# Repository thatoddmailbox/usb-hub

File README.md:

# usb-hub

A four-port USB 2.0 hub based around the [CoreChips SL2.1A](https://datasheet.lcsc.com/szlcsc/1811151645_CoreChips-SL2-1A_C192893.pdf) IC.

You can choose whether it's bus powered or externally powered with JP1. Soldering JP1 closed selects bus power, while leaving JP1 open means devices are powered with external power, which can be provided through J2.

Note that an external 12 MHz crystal is provided for the SL2.1A. The datasheet claims that the chip also has an internal 12 MHz oscillator that you can use by connecting XIN (pin 16 of the SL2.1) to ground. It's recommended to use the external one, though, as it's more stable. (see the red Chinese text on page 5 of the datasheet)

The port closest to the upstream mini-USB port is port number 1, and the remaining ports are numbered 2 through 4.

## Assembly
This board is fairly easy to assemble with a soldering iron, flux, and solder wick. The main thing to watch out for is that the two sets of electrolytic capacitors, near the output ports, have opposite polarities. The silkscreen has the positive side labeled, so you should make sure the negative side of the capacitor (with the black stripe) is opposite of the positive side (as labeled by a plus on the board).

## Useful links
* [Rev 0 schematic](./mfg/rev0/usb-hub.pdf)
* [Rev 0 BOM](./mfg/rev0/usb-hub.csv)

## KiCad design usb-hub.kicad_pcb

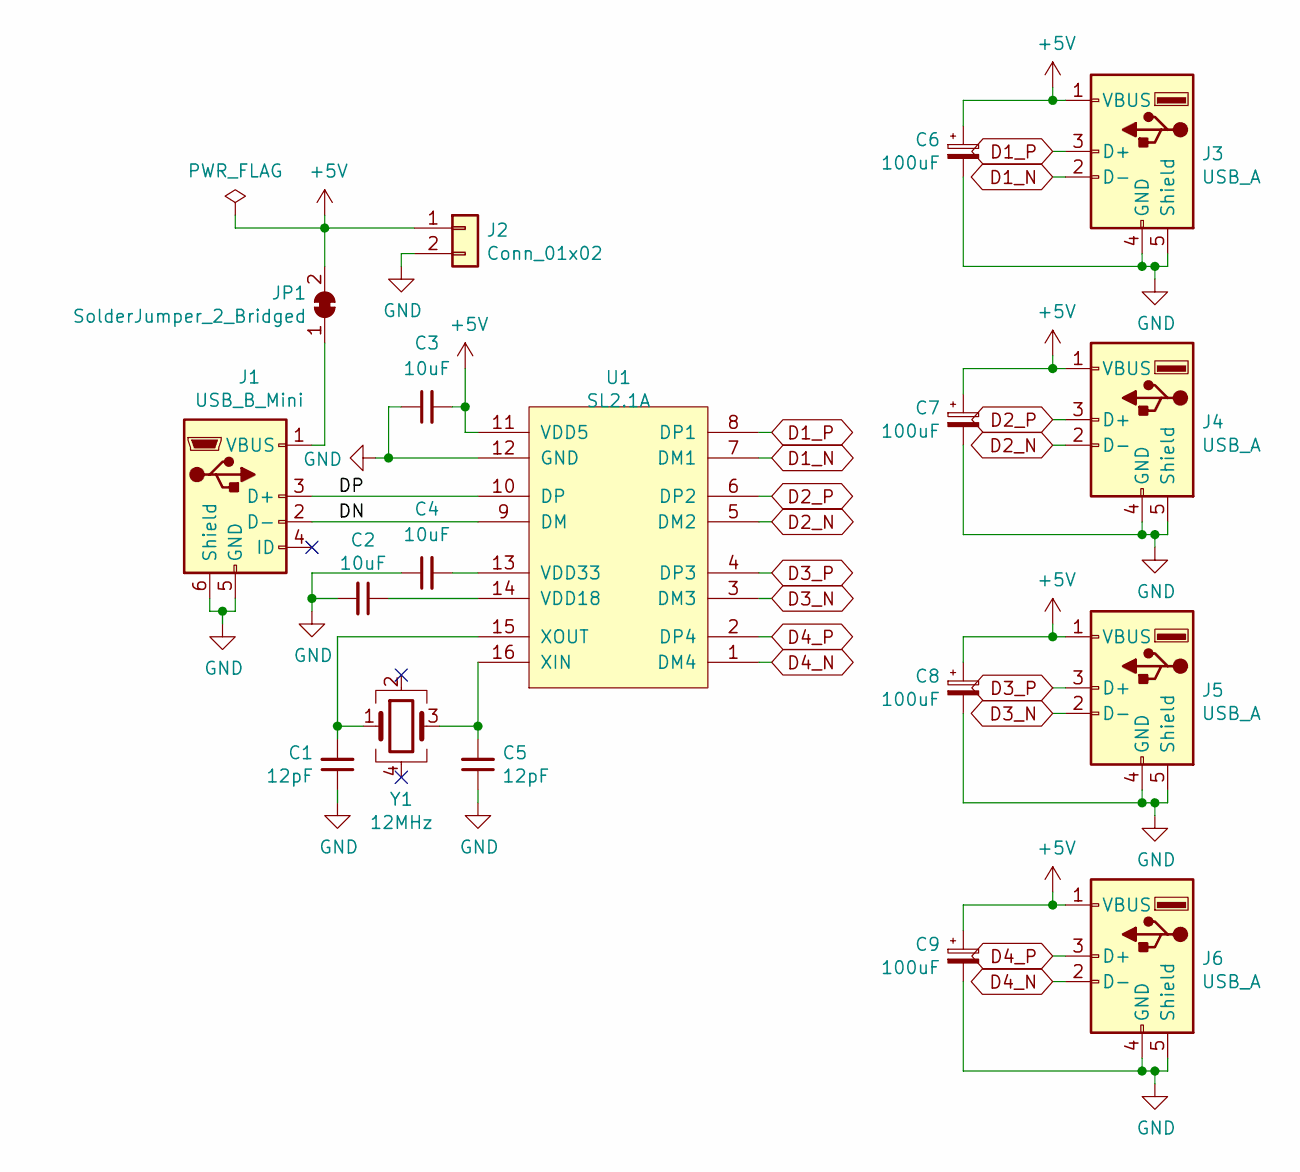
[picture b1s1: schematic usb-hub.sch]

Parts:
C1, C5: 12pF; C_0603_HandSoldering
C2, C3, C4: 10uF; C_0603_HandSoldering
C6, C7, C8, C9: 100uF; CP_Elec_6.3x5.3
J1: USB_B_Mini; USB_Mini-B
J2: Conn_01x02; Pin_Header_Straight_1x02_Pitch2.54mm
J3, J4, J5, J6: USB_A
JP1: SolderJumper_2_Bridged; SolderJumper-2_P1.3mm_Open_TrianglePad1.0x1.5mm
U1: SL2.1A; SOIC-16_3.9x9.9mm_Pitch1.27mm
Y1: 12MHz; Crystal_SMD_3225-4pin_3.2x2.5mm_HandSoldering

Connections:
+5V: C3.2, C6.1, C7.1, C8.1, C9.1, J2.1, J3.1 (VBUS), J4.1 (VBUS), J5.1 (VBUS), J6.1 (VBUS), JP1.2 (B), U1.11 (VDD5)
/DN: J1.2 (D-), U1.9 (DM)
/DP: J1.3 (D+), U1.10 (DP)
D1_N: J3.2 (D-), U1.7 (DM1)
D1_P: J3.3 (D+), U1.8 (DP1)
D2_N: J4.2 (D-), U1.5 (DM2)
D2_P: J4.3 (D+), U1.6 (DP2)
D3_N: J5.2 (D-), U1.3 (DM3)
D3_P: J5.3 (D+), U1.4 (DP3)
D4_N: J6.2 (D-), U1.1 (DM4)
D4_P: J6.3 (D+), U1.2 (DP4)
GND: C1.1, C2.2, C3.1, C4.1, C5.1, C6.2, C7.2, C8.2, C9.2, J1.5 (GND), J1.6 (Shield), J2.2, J3.4 (GND), J3.5 (Shield), J4.4 (GND), J4.5 (Shield), J5.4 (GND), J5.5 (Shield), J6.4 (GND), J6.5 (Shield), U1.12 (GND)
unnamed: C1.2, U1.15 (XOUT), Y1.1
unnamed: C2.1, U1.14 (VDD18)
unnamed: C4.2, U1.13 (VDD33)
unnamed: C5.2, U1.16 (XIN), Y1.3
unnamed: J1.1 (VBUS), JP1.1 (A)

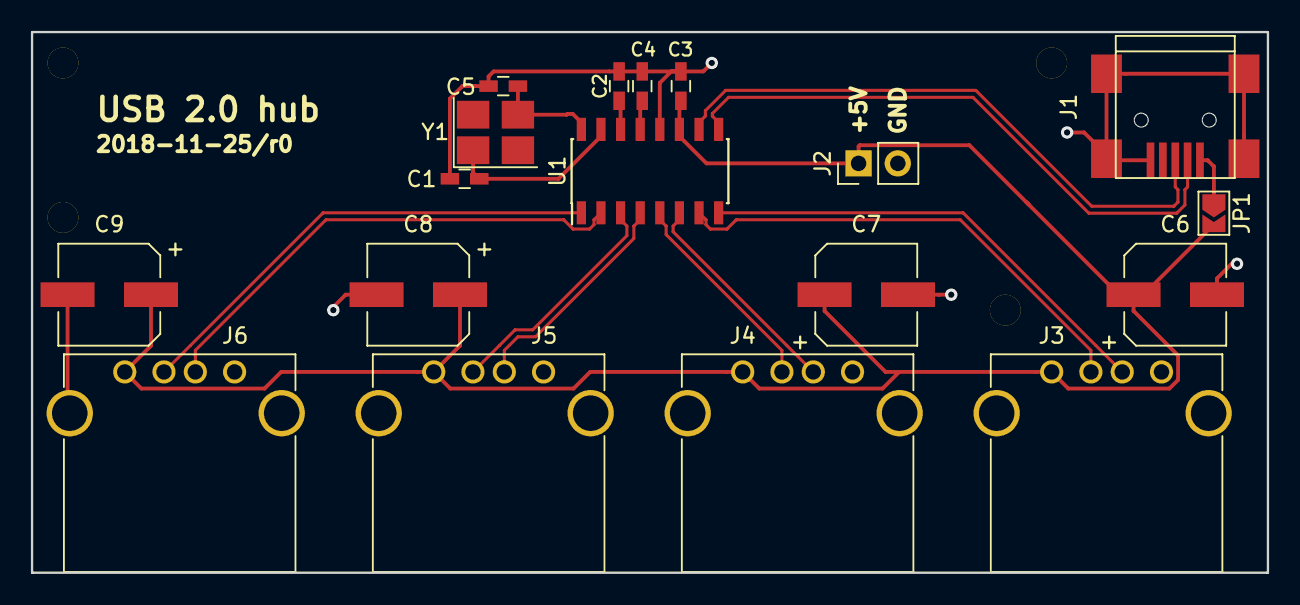
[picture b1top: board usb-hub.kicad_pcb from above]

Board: 2 copper layers, 80.0 x 35.0 mm, 18 parts (0 on the bottom side), 17 nets.

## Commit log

2021-02-12 commit rev 0 schematic, pcb, and gerbers
2021-02-12 add README
2021-02-12 readme: add a description
2021-02-12 readme: add chip name and link
2021-02-12 add pdf of rev 0 schematic
2021-02-12 add csv bom file for rev 0
2021-02-12 move manufacturing files into rev0 folder
2021-02-12 readme: add links to schematic and bom
2021-02-12 readme: note about bus/external power
2021-02-12 add LICENSE
2021-02-13 readme: mention internal 12 MHz oscillator
2021-02-13 readme: mention the pin to use for internal xtal
2021-02-13 readme: refer to datasheet's claims about internal vs external xtal stability
2021-02-13 readme: add assembly section
2021-02-15 readme: add info on port numbering
2021-02-15 readme: small edits to port numbering section
2021-02-15 add picture of hub
2021-02-15 crop image
2021-02-15 crop image some more
2021-02-15 readme: add image
2021-02-15 readme: make image smaller
2026-06-20 add step file for rev 0
2026-06-21 add case files (freecad project and stls)
